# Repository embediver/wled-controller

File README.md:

# A simple, ESP-07 based, controller for NeoPixel LED's 
Designed to work with all kinds of single wire adressable NeoPixel LEDs and ATX Power supplies.

* Works great with [WLED](https://github.com/Aircoookie/WLED)
* Support for IR Remotes
* Two-Layer PCB designed for home production
* 74HTC00 as Levelshifter
* Output to Toggle PS-ON pin of ATX power supplies
* Over voltage protection on I/O ports

It's intended to be uesed with ATX power supplies (since they are so easy availible), where it can be driven over the 5V always-on rail.
By powering the LED's with the other Rails, they can be switched off together with the PS.

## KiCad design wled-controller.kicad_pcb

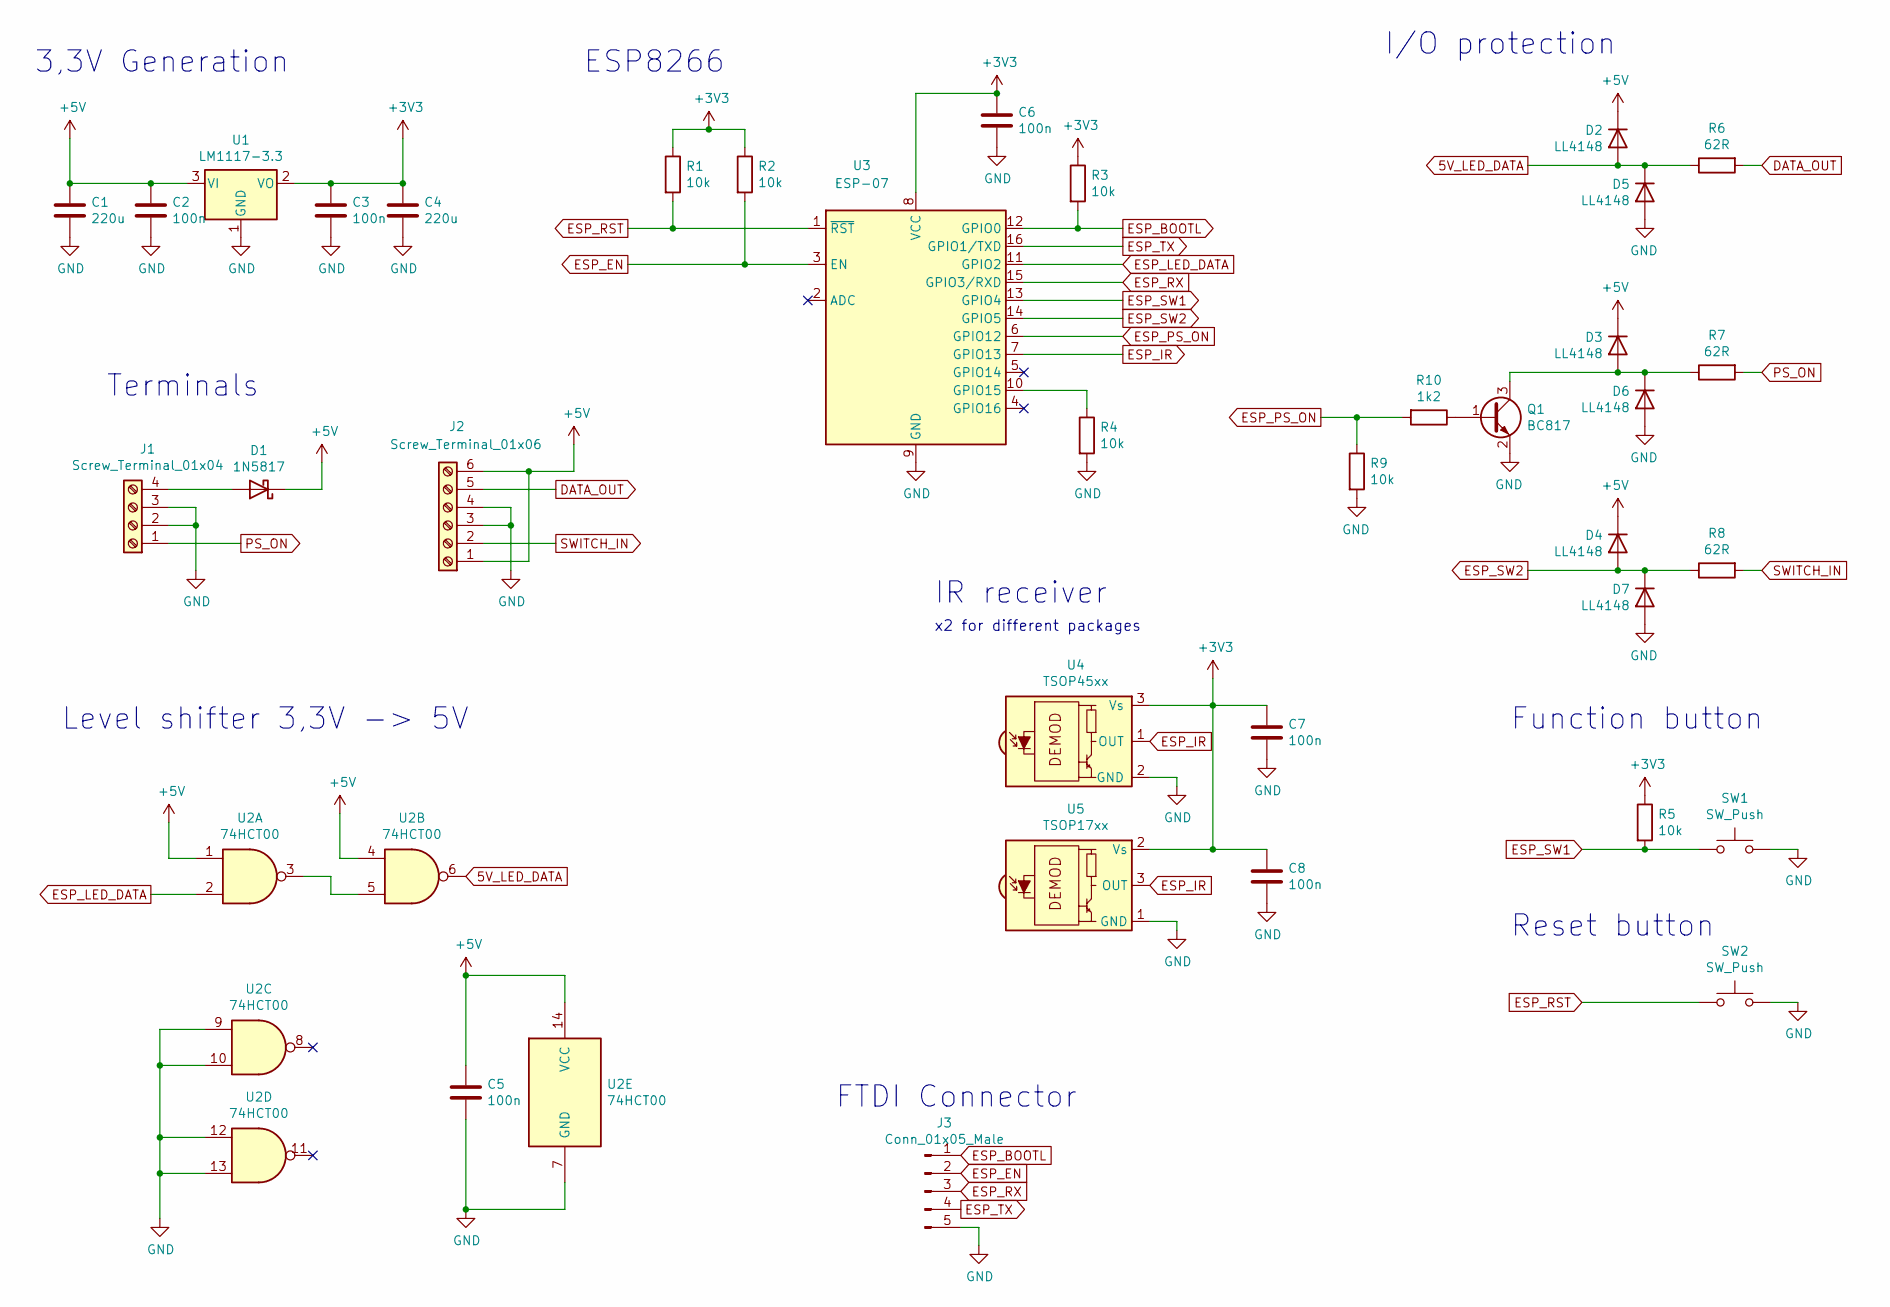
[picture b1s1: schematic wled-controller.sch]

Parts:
C1, C4: 220u; CP_Radial_D8.0mm_P3.50mm
C2, C3, C5, C6, C7, C8: 100n; C_0805_2012Metric_Pad1.18x1.45mm_HandSolder
D1: 1N5817; D_DO-41_SOD81_P10.16mm_Horizontal
D2, D3, D4, D5, D6, D7: LL4148; D_MiniMELF
J1: Screw_Terminal_01x04; TerminalBlock_4Ucon_1x04_P3.50mm_Horizontal
J2: Screw_Terminal_01x06; TerminalBlock_4Ucon_1x06_P3.50mm_Horizontal
J3: Conn_01x05_Male; PinHeader_1x05_P2.54mm_Vertical
Q1: BC817; SOT-23
R1, R2, R3, R4, R5, R9: 10k; R_0805_2012Metric_Pad1.20x1.40mm_HandSolder
R6, R7, R8: 62R; R_0805_2012Metric_Pad1.20x1.40mm_HandSolder
R10: 1k2; R_0805_2012Metric_Pad1.20x1.40mm_HandSolder
SW1, SW2: SW_Push; SW_PUSH_6mm_H13mm
U1: LM1117-3.3; SOT-223-3_TabPin2
U2: 74HCT00; SO-14_3.9x8.65mm_P1.27mm
U3: ESP-07; ESP-07v2
U4: TSOP45xx; Vishay_MOLD-3Pin
U5: TSOP17xx; Vishay_CAST-3Pin

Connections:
5V_LED_DATA: D2.2 (A), D5.1 (K), R6.1, U2.6
+3V3: C3.1, C4.1, C6.1, C7.1, C8.1, R1.1, R2.1, R3.1, R5.1, U1.2 (VO), U3.8 (VCC), U4.3 (Vs), U5.2 (Vs)
+5V: C1.1, C2.1, C5.1, D1.1 (K), D2.1 (K), D3.1 (K), D4.1 (K), J2.1, J2.6, U1.3 (VI), U2.1, U2.4, U2.14 (VCC)
DATA_OUT: J2.5, R6.2
ESP_BOOTL: J3.1, R3.2, U3.12 (GPIO0)
ESP_EN: J3.2, R2.2, U3.3 (EN)
ESP_IR: U3.7 (GPIO13), U4.1 (OUT), U5.3 (OUT)
ESP_LED_DATA: U2.2, U3.11 (GPIO2)
ESP_PS_ON: R9.1, R10.2, U3.6 (GPIO12)
ESP_RST: R1.2, SW2.1, U3.1 (~RST)
ESP_RX: J3.3, U3.15 (GPIO3/RXD)
ESP_SW1: R5.2, SW1.1, U3.13 (GPIO4)
ESP_SW2: D4.2 (A), D7.1 (K), R8.1, U3.14 (GPIO5)
ESP_TX: J3.4, U3.16 (GPIO1/TXD)
GND: C1.2, C2.2, C3.2, C4.2, C5.2, C6.2, C7.2, C8.2, D5.2 (A), D6.2 (A), D7.2 (A), J1.2, J1.3, J2.3, J2.4, J3.5, Q1.2 (E), R4.2, R9.2, SW1.2, SW2.2, U1.1 (GND), U2.7 (GND), U2.9, U2.10, U2.12, U2.13, U3.9 (GND), U4.2 (GND), U5.1 (GND)
unnamed: D1.2 (A), J1.4
unnamed: D3.2 (A), D6.1 (K), Q1.3 (C), R7.1
unnamed: Q1.1 (B), R10.1
unnamed: R4.1, U3.10 (GPIO15)
unnamed: U2.3, U2.5
PS_ON: J1.1, R7.2
SWITCH_IN: J2.2, R8.2

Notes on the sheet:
3,3V Generation
ESP8266
Function button
Reset button
IR receiver
x2 for different packages
Level shifter 3,3V -> 5V
I/O protection
Terminals
FTDI Connector

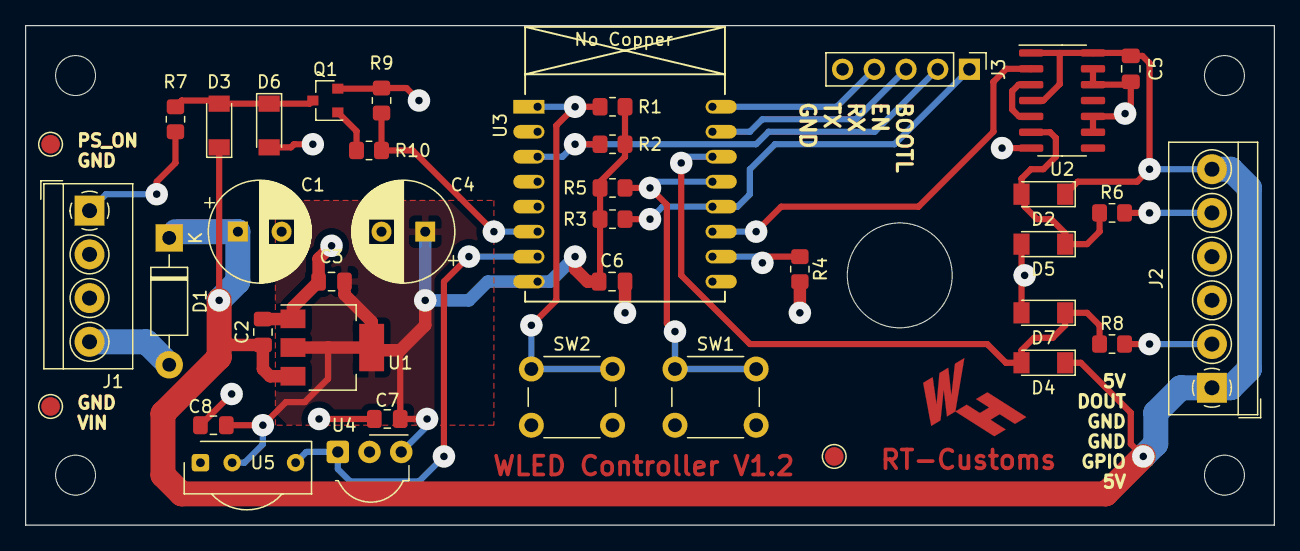
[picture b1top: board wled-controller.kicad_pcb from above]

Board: 2 copper layers, 100.0 x 40.0 mm, 36 parts (0 on the bottom side), 22 nets.

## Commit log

2021-10-08 First routing.
2021-10-09 V1.0
2021-10-09 saved progress correctly
2021-10-11 Rev 2 with open Collector PS switch
2021-10-11 Moved ESP to not stick over board side.
2021-10-11 .3mf case files.
    And minor silkscreen improvement.
2021-10-11 Fix unconnected pad & silkscreen placement
2021-10-12 Generated RT-Lab manufactoring data.
2021-10-12 Changed input diode to 1N5817.
2021-10-13 Minor improvements.
2021-10-13 Changed programming header to 2.54mm
2021-10-14 Added README and schematic pdf
2021-10-27 Reduced board length to 100mm.
    Improved and added Silkscreen features.
